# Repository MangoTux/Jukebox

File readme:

The files in here are for the jukebox I designed as a gift. 

I'll admit that the python code isn't terribly pythonic. I was working under immense time pressure to finish the project, and focused more on functioning code.
I also designed the circuit in the /board directory, using OSHPark to print it. I've taken some EE courses, but this was an entirely new experience to design and test.

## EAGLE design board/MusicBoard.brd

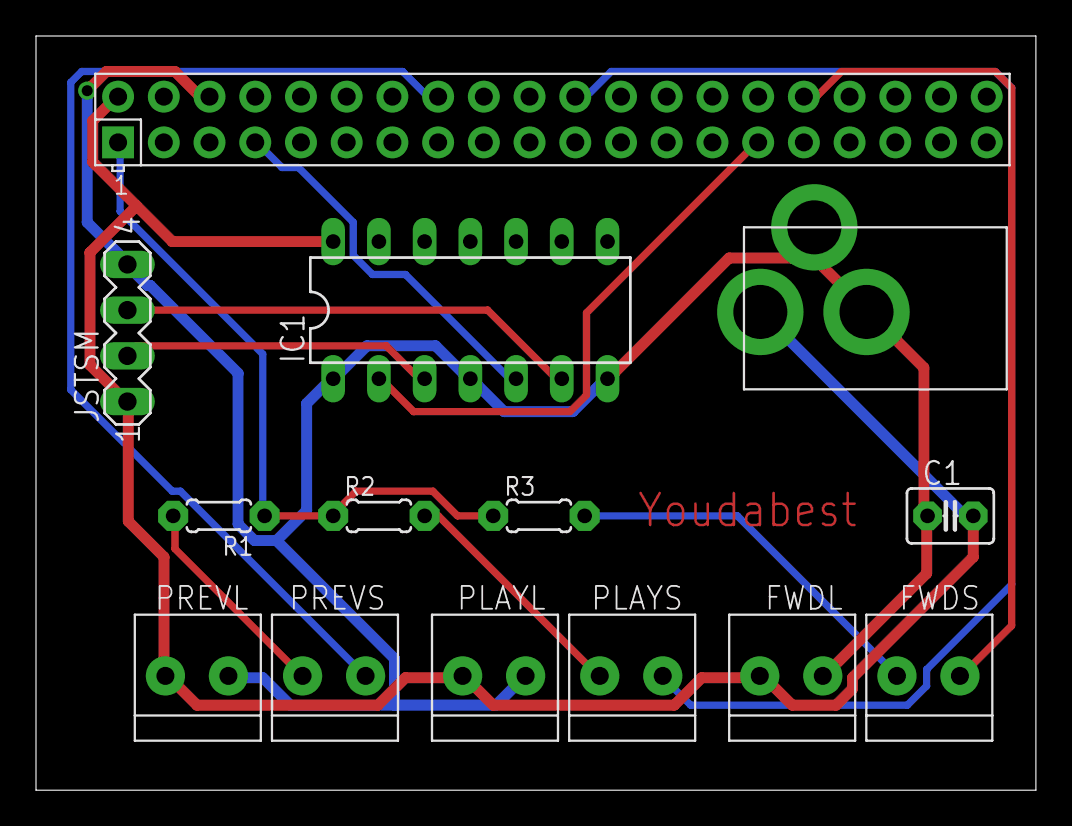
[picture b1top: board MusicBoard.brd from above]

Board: 2 copper layers, 55.6 x 41.9 mm, 14 parts (0 on the bottom side), 13 nets.

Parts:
C1: .1 uF; C2.5-3
FWDL: 1X2-3.5MM
FWDS: 1X2-3.5MM
IC1: 74125N; DIL14
JSTSM: MA04-1
PLAYL: 1X2-3.5MM
PLAYS: 1X2-3.5MM
POWER: 2.1MMJACKTHM; PJ-102A
PREVL: 1X2-3.5MM
PREVS: 1X2-3.5MM
R1, R2, R3: 1000ohm; 0204/5
X1: RASPI_BOARD_B+_E0; RASPI_BOARD_B+_EDGES_0DRILL

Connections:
CIN: IC1.5, X1.7
COUT: IC1.6, JSTSM.3
DIN: IC1.2, X1.29
DOUT: IC1.3, JSTSM.2
GND: C1.1, FWDL.1, IC1.1, IC1.4, IC1.7, JSTSM.4, PLAYL.1, POWER.RING, POWER.RING_SW, PREVL.1, X1.6
unnamed: PREVS.2, R1.2
unnamed: PLAYS.2, R2.2
unnamed: FWDS.2, R3.2
PWR: C1.2, FWDL.2, IC1.14, JSTSM.1, PLAYL.2, POWER.TIP, PREVL.2, X1.2
PWRSWITCH: R1.1, R2.1, R3.1, X1.1
SWITCH_FWD: FWDS.1, X1.32
SWITCH_PLAY: PLAYS.1, X1.22
SWITCH_PREV: PREVS.1, X1.16

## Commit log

2015-12-31 Added musicPlayer
2015-12-31 Added EAGLE files to project
2015-12-31 Comment fix
2015-12-31 Renamed file
